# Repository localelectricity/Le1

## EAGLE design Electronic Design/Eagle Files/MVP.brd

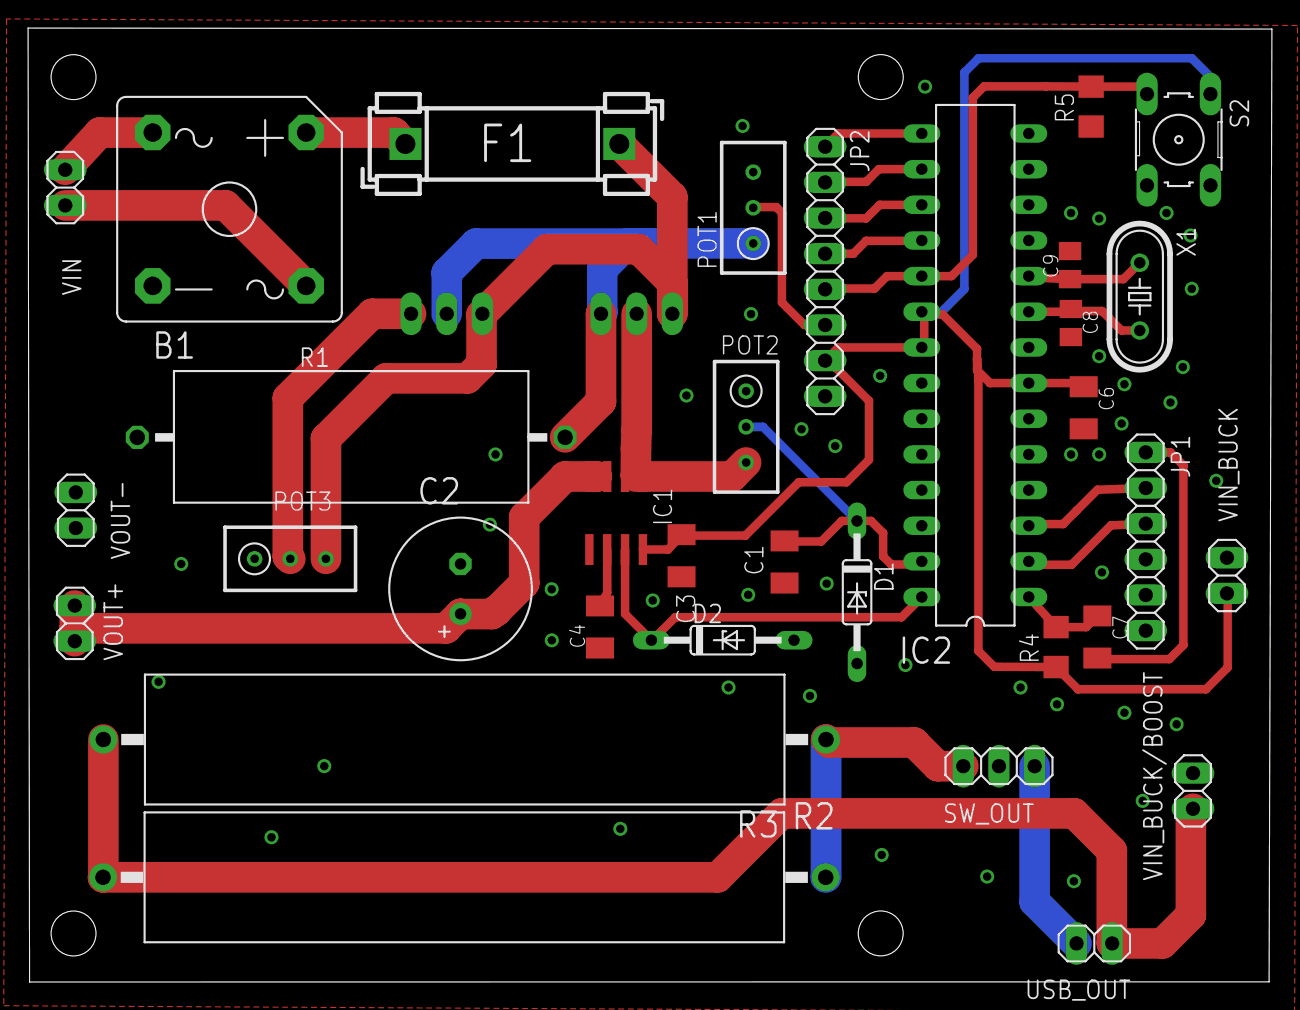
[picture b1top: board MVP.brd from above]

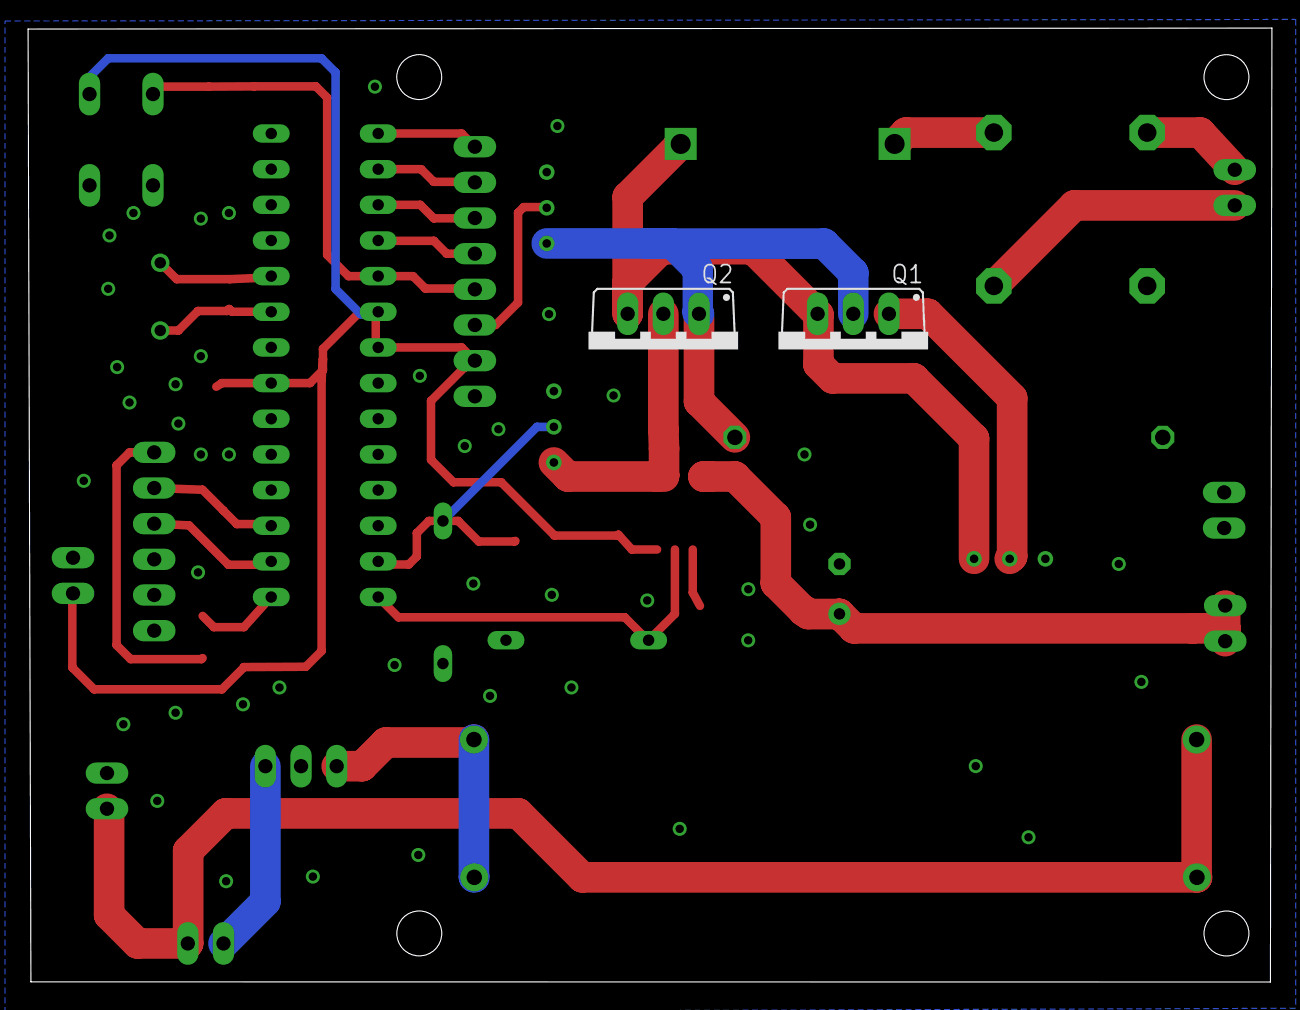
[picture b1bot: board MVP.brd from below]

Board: 2 copper layers, 88.6 x 68.0 mm, 35 parts (2 on the bottom side), 28 nets.

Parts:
B1: KBPC610; GBPC6
C1: 10n; C1206K
C2: 220uF; E3,5-10
C3, C4, C7: 0.1u; C1206K
C6: 10u; C1206K
C8, C9: 22n; C0805K
D1, D2: 5.1V; DO35Z10
F1: FUSEBLANK_5X20MM; FUSE_HOLDER_5X20MM
IC1: ACS712ELC-5A; SOIC8
IC2: ATMEGA328-PU; DIL28-3
JP1: 1X06
JP2: 1X08
POT1, POT2: 500k; RTRIM3296W
POT3: 5k; RTRIM3296W
Q1, Q2: IRF9540; TO220BV
R1: 1k; VTA52
R2, R3: 22R; RWM8X45
R4, R5: 10k; R1206
S2: B3F-10XX
SW_OUT: 1X03
USB_OUT: 1X02
VIN: 1X02
VIN_BUCK: 1X02
VIN_BUCK/BOOST: 1X02
VOUT+: 1X02
VOUT-: 1X02
X1: 16MHz; HC49/S

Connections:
+5V: C3.1, C6.1, IC1.8, IC2.7, IC2.20, IC2.21, JP2.7, R4.1, S2.1, VIN_BUCK.1
GND: B1.-, C1.2, C2.-, C3.2, C4.1, C6.2, C8.2, C9.2, D1.A, D2.A, IC1.5, IC2.8, IC2.22, JP1.6, JP2.8, POT1.3, POT2.1, POT3.1, R1.1, R5.1, SW_OUT.2, VIN_BUCK.2, VIN_BUCK/BOOST.2, VOUT-.1, VOUT-.2
IIN: D2.C, IC1.7, IC2.28
M1S: C2.+, IC1.3, IC1.4, VOUT+.1, VOUT+.2
unnamed: B1.+, F1.1
unnamed: C4.2, IC1.6
unnamed: IC1.1, IC1.2, POT2.3, Q2.D
unnamed: IC2.3, JP1.2
unnamed: IC2.2, JP1.3
unnamed: IC2.15, JP2.1
unnamed: POT3.2, Q1.G
unnamed: IC2.19, JP2.5, R5.2, S2.3
unnamed: IC2.16, JP2.2
unnamed: F1.2, POT3.3, Q1.S, Q2.S
unnamed: IC2.17, JP2.3
unnamed: IC2.18, JP2.4
unnamed: C7.2, JP1.1
unnamed: C9.1, IC2.10, X1.1
unnamed: C8.1, IC2.9, X1.2
unnamed: C7.1, IC2.1, R4.2
unnamed: B1.AC2, VIN.2
unnamed: B1.AC1, VIN.1
unnamed: R2.2, R3.2, USB_OUT.1, VIN_BUCK/BOOST.1
unnamed: R2.1, R3.1, SW_OUT.3
unnamed: SW_OUT.1, USB_OUT.2
unnamed: POT1.1, Q1.D, Q2.G, R1.2
OVERV: JP2.6, POT1.2
VIN: C1.1, D1.C, IC2.27, POT2.2
